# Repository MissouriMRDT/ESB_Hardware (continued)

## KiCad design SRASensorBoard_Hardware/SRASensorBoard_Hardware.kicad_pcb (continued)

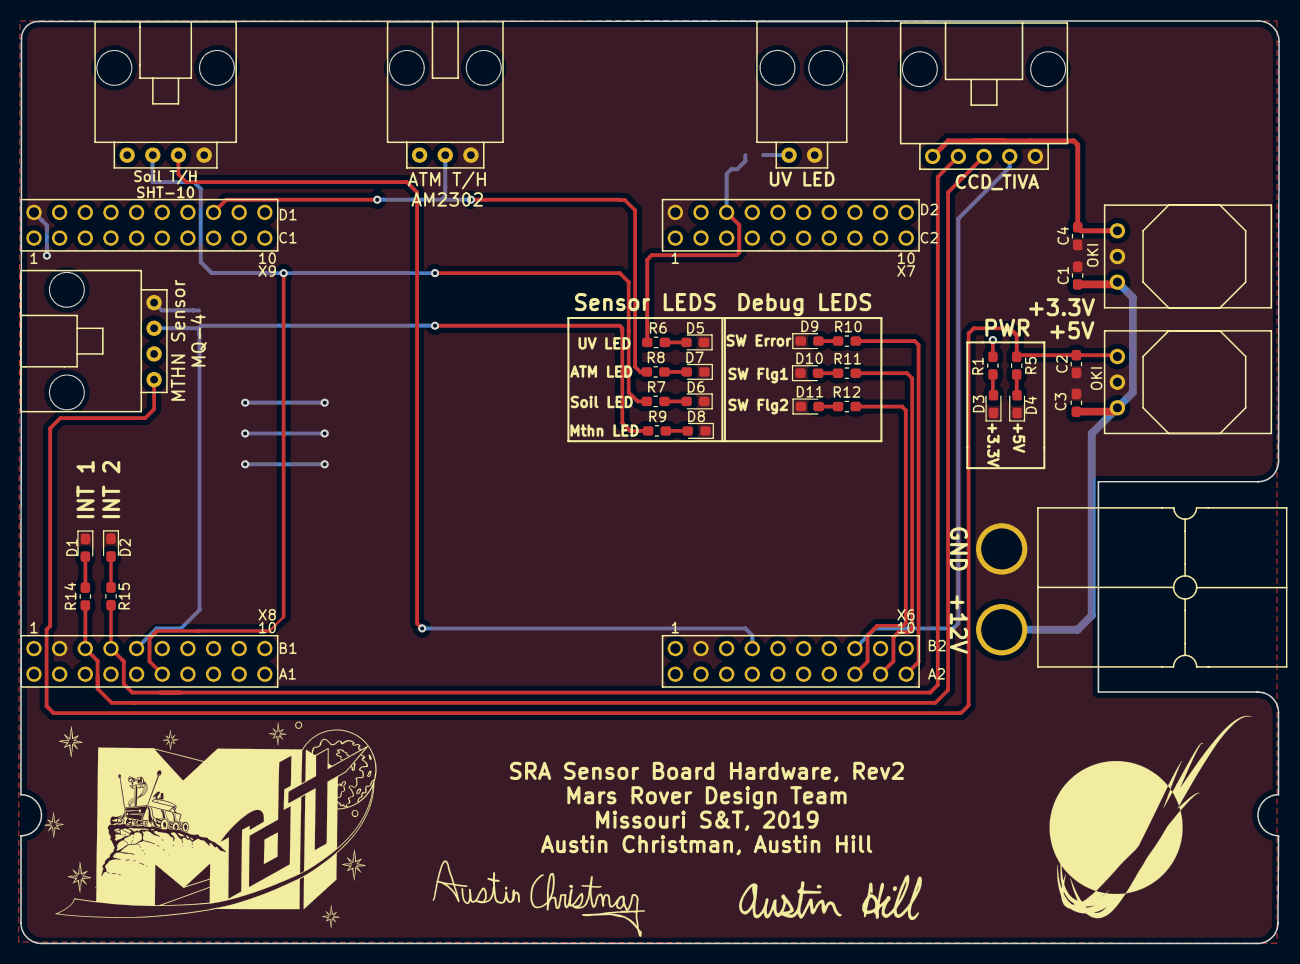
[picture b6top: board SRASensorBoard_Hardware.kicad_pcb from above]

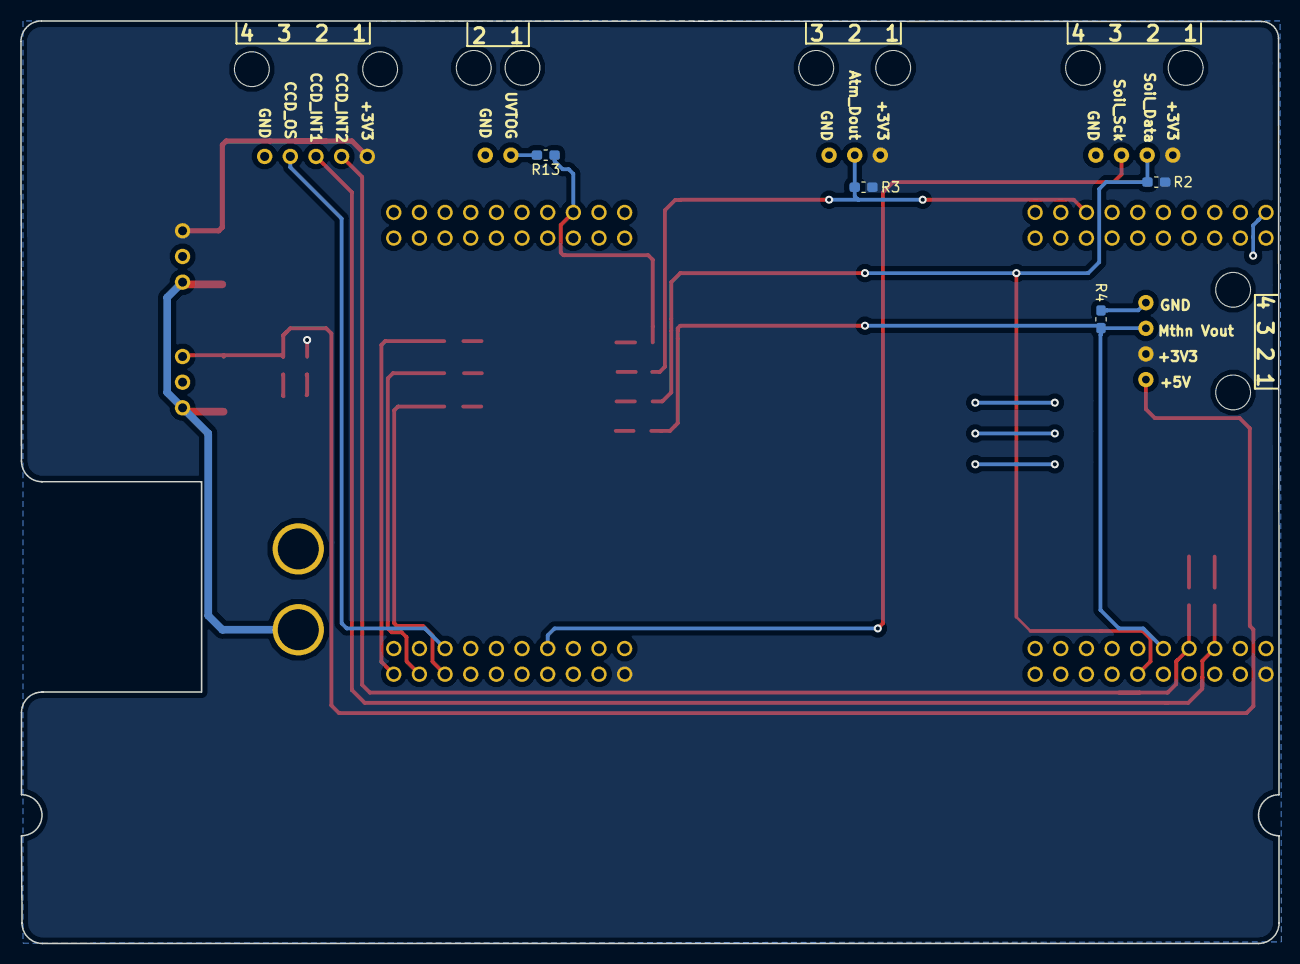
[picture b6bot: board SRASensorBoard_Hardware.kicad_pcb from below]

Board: 2 copper layers, 124.6 x 91.3 mm, 39 parts (4 on the bottom side), 27 nets.

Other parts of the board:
D2: LED; D_0603_1608Metric_Pad1.05x0.95mm_HandSolder
R15: 500; R_0603_1608Metric_Pad1.05x0.95mm_HandSolder

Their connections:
CCD_INT2: R15.1; also elsewhere on the board
GND: D2.1; also elsewhere on the board
unnamed: D2.2, R15.2

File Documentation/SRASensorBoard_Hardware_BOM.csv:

Id,Designator,Package,Designation,,Item Name,Part Number,,,Vendor,Quantity,Cost Per Item,,,URL,Comments
1,Conn1,Anderson_2_Horisontal_Side_by_Side,AndersonPP,,Anderson Power 1336G1 Printed Circuit Board High Power 45 Amp Horizontal Bottom Contact,1336G1,,,Powerwerx,2,0.53,,,https://powerwerx.com/anderson-1336g1-printed-circuit-board-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,
2,Conn1,Anderson_2_Horisontal_Side_by_Side,AndersonPP,,PP15/30/45 Loose Piece Powerpole Colored Housing,1327,,,Powerwerx,1,0.37,,,https://powerwerx.com/anderson-powerpole-colored-housings ,
3,Conn1,Anderson_2_Horisontal_Side_by_Side,AndersonPP,,PP15/30/45 Loose Piece Powerpole Colored Housing,1327G6,,,Powerwerx,1,0.37,,,https://powerwerx.com/anderson-powerpole-colored-housings,
4,"Conn8,Conn7",MOLEX_SL_08_Horizontal,Molex_SL_08,,CONN HEADER 8POS .100 R/A 30AU ,WM4159-ND,,,Digikey,2,1.84,,,https://www.digikey.com/product-detail/en/molex-connector-co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,
5,R4,R_0603_1608Metric_Pad1.05x0.95mm_HandSolder,22K,,RES SMD 22K OHM 5% 1/4W 0603 ,RHM22KDCT-ND,,,Digikey,1,0.1,,,https://www.digikey.com/product-detail/en/rohm-semiconductor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,
6,"R2,R3",R_0603_1608Metric_Pad1.05x0.95mm_HandSolder,10K,,RES SMD 10K OHM 1% 1/4W 0603,RHM10KADCT-ND,,,Digikey,2,0.14,,,https://www.digikey.com/product-detail/en/rohm-semiconductor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,
7,"R1,R5,R6,R7,R8,R9,R10,R11,R12,R13",R_0603_1608Metric_Pad1.05x0.95mm_HandSolder,500,,RES SMD 510 OHM 5% 1/4W 0603 ,RHM510DCT-ND,,,Digikey,10,0.1,,,https://www.digikey.com/product-detail/en/rohm-semiconductor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,
8,Conn2,MOLEX_SL_04_Horizontal,Soil Temp/Moist,,CONN HEADER 4POS .100 R/A GOLD,WM4902-ND,,,Digikey,1,1.16,,,https://www.digikey.com/products/en?keywords=WM4902-ND,
9,Conn3,MOLEX_SL_03_Horizontal,Air Temp/Humid,,CONN HEADER 3POS .100 R/A GOLD ,WM4901-ND,,,Digikey,1,1.12,,,https://www.digikey.com/products/en?keywords=WM4901-ND,
10,Conn4,MOLEX_SL_04_Horizontal,Methane_Sensor,,CONN HEADER 4POS .100 R/A GOLD,WM4902-ND,,,Digikey,1,1.16,,,https://www.digikey.com/products/en?keywords=WM4902-ND,
11,Conn5,MOLEX_SL_05_Horizontal,Molex_SL_05,,CONN HEADER 5POS .100 R/A GOLD ,WM4903-ND,,,Digikey,1,1.21,,,https://www.digikey.com/products/en?keywords=WM4903-ND,
12,Conn6,MOLEX_SL_02_Horizontal,UV_LED,,CONN HEADER 2POS .100 R/A GOLD ,WM4900-ND,,,Digikey,1,0.72,,,https://www.digikey.com/products/en?keywords=WM4900-ND,
13,U1,Through Hole Headers,Headers,,CONN HDR 20POS 0.1 GOLD PCB,S6106-ND,,,Digikey,4,1.26,,,https://www.digikey.com/product-detail/en/sullins-connector-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,
14,"C1,C2,C3,C4",C_0603_1608Metric_Pad1.05x0.95mm_HandSolder,10u,,CAP CER 10UF 6.3V X5R 0603,1276-1119-1-ND,,,Digikey,4,0.15,,,https://www.digikey.com/product-detail/en/samsung-electro-me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,
15,Conn9,MOLEX_SL_04_Horizontal,Molex_SL_04,,CONN HEADER 4POS .100 R/A GOLD,WM4902-ND,,,Digikey,1,1.16,,,https://www.digikey.com/products/en?keywords=WM4902-ND,
16,"D3,D4",D_0603_1608Metric_Pad1.05x0.95mm_HandSolder,LED,,LED GREEN CLEAR SMD,160-1446-1-ND,,,Digikey,2,0.53,,,https://www.digikey.com/product-detail/en/lite-on-inc/LTST-C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,
17,"D5,D6,D7,D8",D_0603_1608Metric_Pad1.05x0.95mm_HandSolder,LED,,LED YELLOW CLEAR SMD,160-1448-1-ND,,,Digikey,4,0.31,,,https://www.digikey.com/product-detail/en/lite-on-inc/LTST-C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,
18,D9,D_0603_1608Metric_Pad1.05x0.95mm_HandSolder,LED,,LED RED CLEAR SMD,160-1447-1-ND,,,Digikey,1,0.29,,,https://www.digikey.com/product-detail/en/lite-on-inc/LTST-C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,
19,"D10,D11",D_0603_1608Metric_Pad1.05x0.95mm_HandSolder,LED,,LED BLUE CLEAR SMD,160-1647-1-ND,,,Digikey,2,0.53,,,https://www.digikey.com/product-detail/en/lite-on-inc/LTST-C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,
20,U1,TM4C129E_Launchpad_X9,~,,EK-TM4C1294XL,296-37267-ND,,,Digikey,1,20.76,,,https://www.digikey.com/products/en?keywords=296-37267-ND,
21,U1,TM4C129E_Launchpad_X9,~,,CONN HDR 20POS 0.1 GOLD PCB,S6106-ND,,,Digikey,4,1.26,,,https://www.digikey.com/product-detail/en/sullins-connector-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,
,,,,,,,,,,,,,,https://www.digikey.com/products/en?mpart=393&v=1528,
22,N/A,N/A,SHT10,,Mesh-protected Weather-proof Temperature/Humidity Sensor - SHT10,1298,,,Adafruit,1,49.95,,,https://www.digikey.com/products/en?mpart=SEN-09404&v=1568,
23,N/A,N/A,AM2302,, SENSOR HUMID/TEMP 5V DTL 2% MOD, 1528-1229-ND,,,Digikey,1,15,,,https://www.mouser.com/ProductDetail/Toshiba/TCD1304DG8ZAW?q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,
24,N/A,N/A,MQ-4,,METHANE CNG GAS SENSOR - MQ-4,1568-1412-ND,,,Digikey,1,4.95,,,,
25,N/A,N/A,CCD,,Image Sensors CCD Linear Sensor 3648 8x20 54mm,757-TCD1304DG8ZAW,,,Mosuer Electronics,1,24.78,,,,

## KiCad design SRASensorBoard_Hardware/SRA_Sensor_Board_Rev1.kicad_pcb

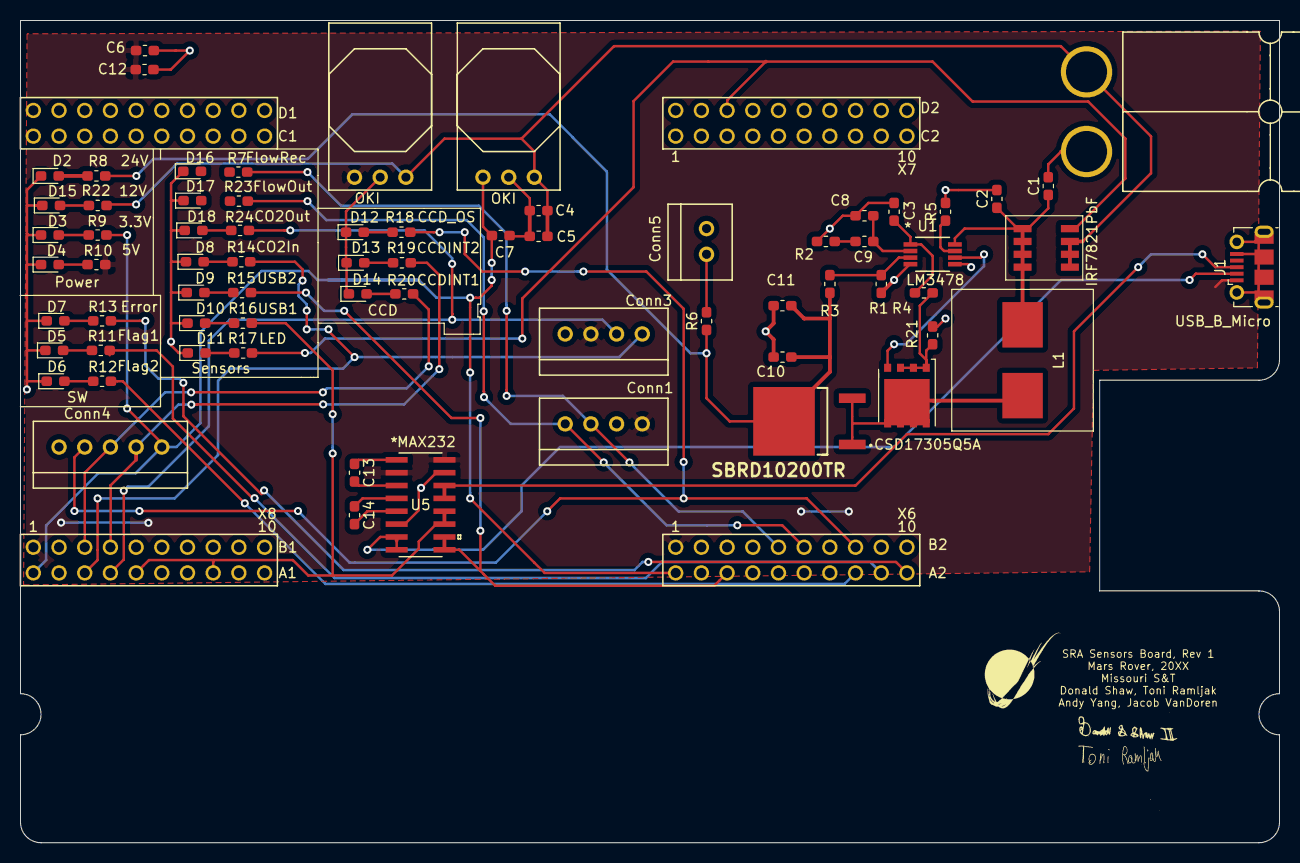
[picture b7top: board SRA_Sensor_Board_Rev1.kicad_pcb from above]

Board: 2 copper layers, 124.5 x 81.3 mm, 72 parts (0 on the bottom side), 51 nets.

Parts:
 : Toni_Signature_Rev4
 #2: Don_Signature_Medium
C1: 120uF; C_0603_1608Metric_Pad1.05x0.95mm_HandSolder
C2: 100nF; C_0603_1608Metric_Pad1.05x0.95mm_HandSolder
C3: 10pF; C_0603_1608Metric_Pad1.05x0.95mm_HandSolder
C4, C5, C6, C7: 10uF; C_0603_1608Metric_Pad1.05x0.95mm_HandSolder
C8: 1nF; C_0603_1608Metric_Pad1.05x0.95mm_HandSolder
C9: 22nF; C_0603_1608Metric_Pad1.05x0.95mm_HandSolder
C10, C11: 82uF; C_0603_1608Metric_Pad1.05x0.95mm_HandSolder
C12, C13, C14: 1uF; C_0603_1608Metric_Pad1.05x0.95mm_HandSolder
Conn1, Conn3: Molex_SL_04; MOLEX_SL_04_Vertical
Conn2: AndersonPP; Anderson_2_Horizontal_Side_by_Side
Conn4: Molex_SL_05; MOLEX_SL_05_Vertical
Conn5: Molex_SL_02; MOLEX_SL_02_Vertical
D1: SBRD10200TR; SMC_DPAK
D2, D3, D4, D5, D6, D7, D8, D9, D10, D11, D12, D13, D14, D15, D16, D17, D18: LED; D_0603_1608Metric_Pad1.05x0.95mm_HandSolder
J1: USB_B_Micro; USB_Micro-B_Molex-105017-0001
L1: 4.7uH 11.2mOhm; Donald_Shaw_SRP1270
Q1: CSD17305Q5A; TDSON-8-1
R1, R3: 18.2k; R_0603_1608Metric_Pad1.05x0.95mm_HandSolder
R2: 3.48k; R_0603_1608Metric_Pad1.05x0.95mm_HandSolder
R4: 100; R_0603_1608Metric_Pad1.05x0.95mm_HandSolder
R5: 26.7k; R_0603_1608Metric_Pad1.05x0.95mm_HandSolder
R6: 3.33; R_0603_1608Metric_Pad1.05x0.95mm_HandSolder
R7, R10, R11, R12, R13, R14, R15, R16, R17, R18, R19, R20, R23, R24: 510; R_0603_1608Metric_Pad1.05x0.95mm_HandSolder
R8: 2500; R_0603_1608Metric_Pad1.05x0.95mm_HandSolder
R9: 330; R_0603_1608Metric_Pad1.05x0.95mm_HandSolder
R21: 6m; R_0603_1608Metric_Pad1.05x0.95mm_HandSolder
R22: 1000; R_0603_1608Metric_Pad1.05x0.95mm_HandSolder
U1: LM3478; LM3478MMX&slash_NOPB
U2, U3: OKI; OKI_Horizontal
U4: TM4C129E_Launchpad; TM4C129E_Launchpad_FULL_THT_TOP
U5: MAX232; MAX232DR
U6: IRF7821PbF; IRF7821PBF

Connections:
+3V3: C7.1, Conn4.1, R9.1, U3.3, U4.+3V3
+5V: C6.1, C12.1, Conn1.1, Conn3.3, J1.1, R10.1, U2.3, U4.+5V, U5.2, U5.16
+12V: C4.1, C5.1, Conn2.2, R22.1, U2.1, U3.1, U6.1, U6.2, U6.3
+24V: C10.1, C11.1, D1.3, R3.2, R6.1, R8.1
C02_In: Conn3.1, R14.1, U4.PC4
C02_Out: Conn3.2, R24.1, U4.PC5
CCD_INT1: Conn4.3, R20.1, U4.PE0
CCD_INT2: Conn4.2, R19.1, U4.PE1
CCD_OS: Conn4.4, R18.1, U4.PK3
Flow_Output: Conn1.4, R23.1, U4.PK1
Flow_Receive: Conn1.3, R7.1, U4.PK0
GND: C1.2, C2.2, C3.2, C4.2, C5.2, C6.2, C7.2, C8.2, C10.2, C11.2, C12.2, Conn1.2, Conn2.1, Conn3.4, Conn4.5, Conn5.2, D2.1, D3.1, D4.1, D5.1, D6.1, D7.1, D8.1, D9.1, D10.1, D11.1, D12.1, D13.1, D14.1, D15.1, D16.1, D17.1, D18.1, J1.5, J1.6, R1.2, R2.2, R5.2, R21.2, U1.4, U1.5, U2.2, U3.2, U4.GND, U5.6, U5.15
LED_Enable: R17.1, U4.PP5, U6.4
unnamed: C1.1, C2.1, L1.1, U1.8, U6.5, U6.6, U6.7, U6.8
unnamed: C3.1, R4.1, U1.1
unnamed: C8.1, C9.1, U1.2
unnamed: C9.2, R2.1
unnamed: C13.1, U5.1
unnamed: C13.2, U5.3
unnamed: C14.1, U5.4
unnamed: C14.2, U5.5
unnamed: Conn5.1, R6.2
unnamed: D1.1, D1.2, L1.2, Q1.5
unnamed: D2.2, R8.2
unnamed: D3.2, R9.2
unnamed: D4.2, R10.2
unnamed: D5.2, R11.2
unnamed: D6.2, R12.2
unnamed: D7.2, R13.2
unnamed: D8.2, R14.2
unnamed: D9.2, R15.2
unnamed: D10.2, R16.2
unnamed: D11.2, R17.2
unnamed: D12.2, R18.2
unnamed: D13.2, R19.2
unnamed: D14.2, R20.2
unnamed: D15.2, R22.2
unnamed: D16.2, R7.2
unnamed: D17.2, R23.2
unnamed: D18.2, R24.2
unnamed: Q1.1, Q1.2, Q1.3, R4.2, R21.1
unnamed: Q1.4, U1.6
unnamed: R1.1, R3.1, U1.3
unnamed: R5.1, U1.7
SW_ERROR: R13.1, U4.PN4
SW_Flag1: R12.1, U4.PP4
SW_Flag2: R11.1, U4.PN5
USB_Data_1: J1.3, U5.13, U5.14
USB_Data_2: J1.2, U5.7, U5.8
USB_TIVA_1: R16.1, U4.PC6, U4.PC7, U5.11, U5.12
USB_TIVA_2: R15.1, U4.PP0, U4.PP1, U5.9, U5.10

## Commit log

2018-10-20 Update gitignore
2018-11-29 Board Backup
2018-12-01 worked on SRA board review
2018-12-01 Cleaned up Folder
2018-12-07 Retraced SRA Board
2018-12-08 revised more on the pcb for SRA
2018-12-08 More Updates
    Fixed small traceing errors, folder managment, etc.
2018-12-15 Rev1
2018-12-16 Worked on files
2018-12-16 PR ready
2018-12-16 BOM file and gerbs created
2018-12-16 Push
2018-12-18 updated schematic
2018-12-18 Gerbs and BOM
2018-12-18 finished PCB
2018-12-18 Fixed Gerbs
2018-12-18 updated CCD connector
2018-12-19 Random Commit
2019-03-09 Modified CCD connector
2019-03-09 added CCD connector
2019-03-16 Wired CCD
2019-03-16 fixed schematic
2019-03-17 created Gerbs
2019-03-17 updated documentation
2019-03-17 created steps
2019-03-20 Rev 2 rework
    Changed the connectors to vertical, retraced traces, etc.
2019-10-09 2019-2020 board schematic first revision pre PDR
2019-10-10 Started PCb and Made changes to schematic
    Updated schematic with annotated parts, associated footprints for each part, and by generating a netlist.
    Updated PCB by including all major components on the board and some minor.
2019-10-11 Updated for correct buck converter/Added grounds for LEDs/Added 12v indicator led
2019-10-11 Added some footprints and other stuff I honeslty forgot
2019-10-11 Made some new changes
    Added MOSFETS and Buttons to toggle sensors. Schematic and PCB are updated.
2019-10-12 Small Change
    Moved one of the blue lines
2019-11-14 Killed old sensors added new sensors
    Added usb support to the io pins.
2019-11-15 Added sensors and cleaned repo
    Added Flow sensor
    Added C02 sensor
    Removed relay replaced with power mosfet
    Added resistor to the uv LED
    Deleted projects that were not a part of the repo
2019-11-15 Fixed Footprints
2019-11-16 Worked on some tracing
    Commiting so I don't lose progress.
2019-11-16 Signatures added
2019-11-16 More Routing
    mor
2019-11-16 Fixed some more routing
2019-11-16 Changes to board
    LED area is currently being made. Slight changes to wiring. Added schematic for SMD diode. Overall structure is the same.
2019-11-18 Board Update
    Layout is done. All traces are done. LEDs are done.
2019-11-18 Forgot a ground connection
2019-11-20 Cleaned Some Things
    Signatures and shem visual changes
2019-11-21 Added Step Files
2019-11-21 Updates
    Updated traces on board
    Changed resistor values to be in compliance with best practices
    Regenerated STEP and GERBER files for updated board
    Added TIVA and Connections text files
2019-11-24 Some Rev 2 schematic changes. Tivas and indicator leds still need updating
2019-12-04 Schem Changes
2019-12-07 Small changes to schmatic
    Added names to sensors as well as part number if I found one. Schematic has been approved.
2019-12-09 Updates
    Added footprints. Created new board. Something is up with the andersons.
2019-12-10 Board Genral Layout
    General layout is done. Components are organized into groups for easier design.
2019-12-12 Tracing and whatnot
2019-12-12 Added Gerbs and whatnot
2019-12-13 PRR Changes
2019-12-13 PRR Changes prt 2
2019-12-14 Updated Bom"
2019-12-19 generated gerbs
2020-02-15 Rev 2
    Changed to a FT230XS due to communication problems.
    Moved the power resistors because they looked a little to close to
    microcontroller components.
    Made some labels more visible.
    Changed the footprint for the usb to be correct with the component.
2020-02-16 Rev 2 prt 2 changes
    Updated UV led to current format
    Removed CCD
2020-02-17 Forgot to update gerbs
2020-02-17 And Bom
2020-09-14 Created project
2020-10-06 new sensor rev 2
    moved to hierarchy and added new power circuits
2020-10-12 Committed rev1 to rev1 branch instead of master
2020-10-12 Revert "new sensor rev 2"
    This reverts commit 156ab373f26da52bc01a01f00cdb696ec9d5eefa.
2020-10-16 Sciency stuff for the board
    finished!
2020-10-19 Science_sensor reveiw 1
    Yep
2020-11-19 Layout started, edge cut fix
    ladybug is not pleased
2020-11-19 edge cuts fixed
2020-11-19 Board Progress 1
    Board expanded and mosfets are positioned for wiring
2020-11-20 Broad Progress 2-oof
    Pre-oops need to add 6 mosfets for spectrometer
2020-11-23 Board Progress 3
    New mosfets are in but old mosfets need some clean up
2020-11-24 Board Progress 4
    Finished mosfets and cleaned up traces
2020-11-24 Board Progress 5 (First revison)
    Finished Rev 1
2020-11-28 Board Progress 6 (Post Review)
    Finished moving vias off pads and labeling most things and added leds for spectrometer
2020-11-28 Board Progress 7 (final rev 1)
    Final edits for REV 1
2020-11-30 Fixed some library issues
2020-11-30 Fixed Gerbs and step file
2020-12-02 Finished BOM
2020-12-02 Fixed BOM
2020-12-02 Actually fixed the BOM
2021-09-24 Added Tiva and Power
    Put tiva in hierarchal sheet, added okis, 12v anderson and ground anderson to main sheet w/o components.
2021-10-06 Added Okis to board
2021-10-06 Connected andersons 12v and gnd
2021-10-06 Griffin_Buschjost_O2_Sensor
    Copied in O2 Sensor from last year and added global labels to TIVA in pin 3 and 4 for the TIVA O2 RX and TX
2021-10-06 added CO2 sensor and fixed OKIs
2021-10-06 added CO2 TIVA tags
2021-10-06 Methane Sensor & Tiva Pins added
    Added USB A connector and USB to UART converter for CH4 sensor
2021-10-07 Renamed CH4 RX/TX to match with others, swapped tx&rx tiva pins (might be wrong)
2021-10-07 Added NH3 sensor and MOSFETS, fixed tiva pins
2021-10-10 Added software pins and no connects to Tiva
2021-10-10 schematic review meeting
2021-10-15 Made BOM File
2021-10-15 Labeled LED Colors
2021-10-16 Flipped ground symbol
2021-10-22 Made PDF of schematic
2021-11-05 Footprint, Layout started
    Replaced each 480 ohm resistor with 2 240 ohm resistors b/c we could not find 480 in stock. Footprints for board filled out. Organized components that need to be connected near each other, board plac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
2021-11-13 Science CDR changes
    Changed NO to NO2, removed NH3 data lines for analog output and changed power to 5v, added 3 laser and photodiode pairs (mosfet not determined), added uv and lights connectors, updated tiva pins
2021-11-14 Bom edited, Layout updated and organized
    Added components for laser and photodiodes to BOM, finished updating schematic and assigned footprints. Updated netlist and organized layout components
2021-11-14 All changes didn't update
2021-11-15 Created libraries folder and added signature file
2021-11-15 Worked on layout
2021-11-15 Worked on Layout
    finished laser and lights layouts and labeled them
2021-11-15 Layout
2021-11-17 Connected Power
2021-11-17 Added signature and label
2021-11-17 added signature
2021-11-17 Added Silkscreen Layer
    Rearranged and added silkscreen
2021-11-18 CDR changes
2021-12-02 CDR Notes and Changes
    Made made copy of board w/ most connectors on board and traces moved away from board edges, lost signature footprints
2021-12-11 Inspection
2021-12-30 fixed autosave files
2021-12-30 removed rescue libraries
2022-02-11 Started Rev 2, NO sensor schematic
2022-02-16 fixed schematic of mosfets for lasers
2022-02-16 added NO sensor stuff and finished layout
2022-02-17 Cleaned up board a bit, put my signature but others disappeared
2022-02-22 rev 2 changes
2022-02-22 changed resistor values
2022-02-22 added signature and worked on layout
2022-02-22 worked on layout for rev2
2022-02-24 updated resistor values and moved via
2022-03-09 added board mounts and did rev 2 changes
2022-03-10 added teensy
2022-03-11 finished layout
2022-03-11 added labels
2022-03-12 Final Rev 2
2022-04-07 Ch4, No, Photodiode sensor code
2022-04-26 updated BOM
2022-09-13 Started Schematic
    Deleted files from pervious year, created new schematic file
2022-09-13 Teensy wiring
    some labels added for teensy
2022-09-13 Reorganizing, added laser & photodiode sheet
2022-09-13 Teensy Connections
2022-09-16 Lasers
2022-09-16 Created Oxygen and Carbon Dioxide sensors.
2022-09-17 Created NO sensor, NH3 sensor, worked on Mosfets, and created Methane sensor with labels.
2022-09-18 Finished mosfets.
2022-09-20 BOM generated, photodiodes added
2022-09-20 Fixed diode ref / values
2022-09-22 Mosfets added, NO sensor updated, NH3 removed NO2 added
2022-09-23 Changed NO molex to match others
2022-09-23 Schematic Review
2022-09-29 Hierarchal sheets removed, laser control mosfets moved low-side
2022-09-29 Deleting Duplicate Files & Old Hierarchical Sheets
2022-09-29 Updated BOM and annotation
2022-10-01 Made PDF + Documentation folder
2022-10-06 Created servo and started limit switch for microscope.
2022-10-07 Added flurometer breakout folder
2022-10-07 Finished limit switch and 12V motor controller with encoder.
2022-10-07 Started Photodiode schematic.
2022-10-07 Created Fluorometer Light Source breakout schematic.
2022-10-07 Microscope, Fluorometer Breakouts
2022-10-07 Ethernet
2022-10-07 H-Bridge & Teensy Connections
2022-10-07 Fixing ERC errors, Updated BOM
2022-10-11 LED breakout, sensor changes
2022-10-11 LED Resistor Values
2022-10-14 NH3, LED Mosfets
2022-10-14 Footprint Assignment
2022-10-14 ERC fixes
2022-10-14 unsaved changes
2022-10-15 Resistor Values 100>120 & 500>330
2022-10-17 Added 2nd Photodiode, Fixed OpAmp
2022-10-19 Changed Measurement Resistance for NH3 sensor
2022-10-19 Layout created, edge cuts drawn
2022-10-19 Sensor Layout organization.
2022-10-19 UVLED Footprints
2022-10-19 Footprints added in paths
2022-10-20 Mosfets & H-Bridge Organized, Photodiode organized, Footprints for LED
2022-10-21 Layout Organization
2022-10-21 Sensor board layout organization
2022-10-21 Layout Edge Cuts and Organization
2022-10-25 Layout Wiring
2022-10-26 Breakout rearranging, LED wiring
2022-10-27 Breakout Boards
2022-10-29 Labels
2022-10-29 Logo and Names, rearranging for better ground
2022-10-30 Photodiode wire connections and labeling.
2022-10-31 Revert "Photodiode wire connections and labeling."
    This reverts commit 414c0e9564a782f982e7044c884eaa931a5570fb.
2022-10-31 Layout Reviews Changes
2022-10-31 Made molex_sl_06 connector.
2022-10-31 Molex_SL_06
2022-11-01 Fixed Schematic error, Labeled some LEDs
2022-11-06 Flipped 2x3, updated sheet boms
2022-11-11 Changed MolexSL7 on LED breakout to SL6
2022-11-17 Labeling LEDs
2022-12-07 Replaced HBridge & Encoder w/ servo
2022-12-12 CCD, LED changes
2022-12-17 Layout updated for LEDs and Science Sensor Board, schematic for CCD
2022-12-17 Found footprint for CCD
2022-12-29 Started cleaning up layout
2022-12-29 Finished traces
2022-12-29 Cleaned up silkscreens
2022-12-30 Changed teensy footprint
2022-12-30 Generated BOM + Gerbs
2022-12-30 Added indicators to LED breakout + made gerbs
2023-01-18 Flurometer Detector Layout
2023-01-18 missed autosave changes
2023-01-20 made STEP file of main board
2023-04-22 Routing traces
